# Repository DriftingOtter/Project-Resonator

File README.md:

# Project Resonator | *The* Open-Source IEM Initiative
> A love letter to the IEM/CIEM hobby.

**📖 Documentation Website:** [https://driftingotter.github.io/Project-Resonator-Web/](https://driftingotter.github.io/Project-Resonator-Web/)

---

## What is Project Resonator?

Project Resonator is a comprehensive knowledge base and resource repository for the complete design cycle and engineering development of in-ear monitors (IEMs). The project aims to bridge the gap between hobbyist curiosity and professional-grade IEM development by providing both the technical resources and educational foundation needed to understand and create high-fidelity audio devices.

### Core Resources

Project Resonator provides a complete suite of engineering resources:

- **CAD Shell Design Files** — Parametric 3D models for ergonomic IEM housings
- **Crossover Simulation Circuits** — Fully documented acoustic crossover networks in VituixCAD
- **PCB Design Files** — Production-ready circuit board layouts in KiCad format
- **Driver Characterization Data** — Frequency response and impedance measurements for balanced armature, dynamic, and electrostatic drivers

These resources are designed for both DIY enthusiasts exploring personal audio projects and aspiring entrepreneurs researching entry into the IEM market who may lack formal training in acoustics or electrical engineering.

### Educational Framework

Beyond physical assets, Project Resonator's primary value lies in its structured tutorial system that demystifies each stage of IEM development:

- **Driver Technology & Selection** — Understanding the physics and performance characteristics of transducer types
- **Crossover Circuit Design** — Acoustic filter theory and frequency division network topology
- **PCB Engineering in KiCad** — Translating schematic designs into manufacturable circuit boards
- **CAD Modeling for Acoustics** — Shell geometry, acoustic chambers, and sound bore design in Fusion 360

By consolidating these resources into a single, cohesive repository, Project Resonator enables users to understand the technology they use daily and provides a foundation for experimentation, innovation, and research & development in personal audio.

### Open-Source Collaboration

The open-source nature of this project allows the community to contribute to a centralized knowledge base, helping others in the same pursuit by:

- Improving and expanding existing documentation
- Contributing additional design files and measurement data
- Sharing novel tuning approaches and manufacturing techniques
- Building supplementary tools and resources for IEM development

Project Resonator serves as a living resource that evolves with the IEM community, fostering innovation through shared knowledge and collaborative development.

---

## The Reference Design (Template)

While the guides apply to *any* IEM project, we provide a complete set of files for a specific "Reference" model to get you started.

**Configuration:** All-BA 4-Driver (1× Low + 1× Mid + 2× High)

**Drivers:**
- Knowles CI-22955 (Low)
- Knowles BK-26824 (Mid)
- Knowles SWFK-31736 (Highs)

**Target Tuning:** Similar to the *Moondrop x Crinacle DUSK*

**Estimated Build Cost:** ~$200-300

### Reference Crossover Diagram

```mermaid
graph LR
    Input[Source Input] --> Woofer_Path[Woofer Path<br/>CI-22955]
    Input --> Mid_Path[Mid Path<br/>BK-26824]
    Input --> High_Path[High Path<br/>SWFK-31736]
    
    Woofer_Path --> R1[22Ω Series]
    R1 --> C1[4.7µF Parallel]
    C1 --> Woofer[CI-22955<br/>BA Woofer]
    
    Mid_Path --> C2[10µF Series]
    C2 --> R2[22Ω Series]
    R2 --> C3[4.7µF Parallel]
    C3 --> Mids[BK-26824<br/>BA Mids]
    
    High_Path --> T1_Path[Tweeter 1]
    High_Path --> T2_Path[Tweeter 2]
    
    T1_Path --> C4[2.2µF Series]
    C4 --> R3[6.8Ω Parallel]
    R3 --> Tweeter1[SWFK-31736<br/>Unit A]
    
    T2_Path --> C5[2.2µF Series]
    C5 --> R4[22Ω Parallel]
    R4 --> Tweeter2[SWFK-31736<br/>Unit B]
    
    style Woofer fill:#1a1a1a
    style Mids fill:#1a1a1a
    style Tweeter1 fill:#1a1a1a
    style Tweeter2 fill:#1a1a1a
    style Input fill:#1a1a1a
```

**Note:** The reference tuning is highly individualized. The project's purpose is to provide all necessary tools and resources pre-configured, allowing you to use this as a foundation to tune and create an IEM tailored to your preferences.

---

## 🔧 Technologies Used & Software Required

1. **VituixCAD** — Tuning simulation and acoustic crossover design
2. **KiCad** — Schematic and PCB design
3. **Autodesk Fusion 360** — CAD modeling for IEM shells
4. **FPGraphTracer** — Extracting frequency and impedance responses from driver spec sheets

**Additional Resources:**
- [YouTube Playlist: IEM Building Resources](https://youtube.com/playlist?list=PL4ahDGGN5zBFhmGqVUoBdOnjuF_9HXV5L)
- [Full Documentation Website](https://driftingotter.github.io/Project-Resonator-Web/)

---

## 🛠️ Installation & Setup Guide

### VituixCAD Setup

1. Download VituixCAD from [https://kimmosaunisto.net/](https://kimmosaunisto.net/)
2. Install and open the `.vxp` simulation file included in this repository
3. **Fix missing file paths:**
   - You'll likely see "missing file path" errors on first load
   - Click the folder icon next to each `.frd` or `.zma` file slot
   - Navigate to the `BA Driver Spec Sheets` folder in this repo
   - Re-link the appropriate files for each driver

*(This only needs to be done once per project file)*

### Downloading IEM Shell Files

All IEM shell files are hosted externally on **MEGA** due to GitHub's file size limitations.

🔗 **[Download Shell Files from MEGA](https://mega.nz/folder/2Z4WzYDR#g-NULd1YQFsHa81YXLZzIw)**

The archive includes:
- **Ready-To-Print** — `.stl` files for direct 3D printing
- **Fusion-Shell-Models** — Editable `.f3d` files for customization in Fusion 360

---

## 📚 Documentation

Complete guides are available on the [Project Resonator Documentation Website](https://driftingotter.github.io/Project-Resonator-Web/), including:

### Engineering & Design
- [Driver Selection](https://driftingotter.github.io/Project-Resonator-Web/docs/Driver-Selection)
- [Crossover Design](https://driftingotter.github.io/Project-Resonator-Web/docs/Crossover-Design)
- [Crossover Tuning](https://driftingotter.github.io/Project-Resonator-Web/docs/Crossover-Tuning)
- [Component Picking](https://driftingotter.github.io/Project-Resonator-Web/docs/Component-Picking)

### Manufacturing & CAD
- [PCB Design](https://driftingotter.github.io/Project-Resonator-Web/docs/PCB-Design)
- [Shell Design](https://driftingotter.github.io/Project-Resonator-Web/docs/Shell-Design)
- [Shell Material and Manufacturing](https://driftingotter.github.io/Project-Resonator-Web/docs/Shell-Material-and-Manufacturing)

### Project Information
- [Tools & Software](https://driftingotter.github.io/Project-Resonator-Web/docs/Tools-&-Software)
- [Project Goals & Philosophy](https://driftingotter.github.io/Project-Resonator-Web/docs/Project-Goals-Philosophy)
- [Project Licensing and Usage](https://driftingotter.github.io/Project-Resonator-Web/docs/Project-Licensing-and-Usage)
- [FAQ & Troubleshooting](https://driftingotter.github.io/Project-Resonator-Web/docs/FAQ-Troubleshooting)
- [How to Contribute](https://driftingotter.github.io/Project-Resonator-Web/docs/Contribution)

---

## ❓ Can I Use These Files To Build My Own IEM?

**Absolutely.** This project is licensed under **CERN-OHL-W** (weakly reciprocal), which allows you to:

- Build IEMs for personal use
- Modify and improve the designs
- Use this as a foundation for commercial projects

The license maintains the open-source spirit while being permissive enough for commercial applications. For full details, see the [Project Licensing and Usage](https://driftingotter.github.io/Project-Resonator-Web/docs/Project-Licensing-and-Usage) documentation.

**Note:** This design represents a learning journey and is far from perfect—but it provides a solid foundation and realistic look at what an IEM build process entails. Use it as a starting point to avoid some of the mistakes made along the way.

---

## 🤝 Contributing

Project Resonator welcomes contributions from the community! Whether you're improving documentation, adding measurement data, sharing tuning variants, or fixing errors, your input helps everyone.

See the [Contribution Guide](https://driftingotter.github.io/Project-Resonator-Web/docs/Contribution) for details on how to get involved.

---

## 🚧 Current Status & Community Testing

**Important:** The reference design has not yet been physically tested by the project author due to budget constraints (~$300 build cost). If you build this design, your feedback and measurements would be invaluable to the community. Please share your results and listening impressions!

---

## 👨‍💻 Author

**Daksh Kaul** (DriftingOtter)

---

## 🙌 Credits & Acknowledgments

Special thanks to:

- **Head-Fi DIY IEM Community** — For fostering knowledge sharing and experimentation
- **[Kozh](https://www.youtube.com/@kozh4013/videos)** — IEM design tutorials and insights
- **[Kirby Meets Audio](https://youtu.be/QClvPIuW3zI)** — Driver selection and acoustic theory
- **[Crinacle](https://www.youtube.com/watch?v=tCqV3ZRcZ9g)** — Measurement methodology and target curves
- **[Mr.T's Design Graveyard](https://youtu.be/3FGNw28xBr0)** — PCB design techniques

*If I've forgotten to credit you, please reach out—contributions are always acknowledged.*

---

## 📄 License

This project is licensed under **CERN Open Hardware Licence Version 2 - Weakly Reciprocal** (CERN-OHL-W).

See [LICENSE](./LICENSE) or the [Project Licensing Documentation](https://driftingotter.github.io/Project-Resonator-Web/docs/Project-Licensing-and-Usage) for full details.

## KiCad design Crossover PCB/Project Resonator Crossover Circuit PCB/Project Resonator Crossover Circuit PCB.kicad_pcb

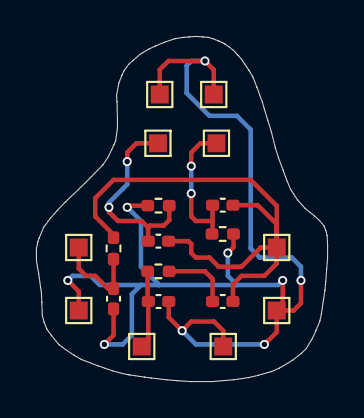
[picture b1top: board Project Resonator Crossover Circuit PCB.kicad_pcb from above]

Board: 2 copper layers, 16.2 x 19.2 mm, 19 parts (0 on the bottom side), 2 nets.

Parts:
C1: 10uF; C_0402_1005Metric_Pad0.74x0.62mm_HandSolder
C2, C6: 2.2uF; C_0402_1005Metric_Pad0.74x0.62mm_HandSolder
C4: 0.10uF; C_0402_1005Metric_Pad0.74x0.62mm_HandSolder
C5: 4.7uF; C_0402_1005Metric_Pad0.74x0.62mm_HandSolder
H1: CI PAD (+); TestPoint_Pad_1.0x1.0mm
H2: CI PAD (-); TestPoint_Pad_1.0x1.0mm
H3: BK PAD (+); TestPoint_Pad_1.0x1.0mm
H4: BK PAD (-); TestPoint_Pad_1.0x1.0mm
H5: SWFK #1 PAD (+); TestPoint_Pad_1.0x1.0mm
H6: SWFK #1 PAD (-); TestPoint_Pad_1.0x1.0mm
H7: SWFK #2 PAD (+); TestPoint_Pad_1.0x1.0mm
H8: SWFK #2 PAD (-); TestPoint_Pad_1.0x1.0mm
H9: SOURCE PAD (+); TestPoint_Pad_1.0x1.0mm
H10: SOURCE PAD (-); TestPoint_Pad_1.0x1.0mm
R2, R5, R6: 22R; R_0402_1005Metric_Pad0.72x0.64mm_HandSolder
R3: 6.8R; R_0402_1005Metric_Pad0.72x0.64mm_HandSolder

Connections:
+: C1.1, C2.1, C2.2, C4.1, C4.2, C5.1, C6.1, C6.2, H1.1, H3.1, H5.1, H7.1, H9.1, R2.1, R2.2, R3.1, R5.1, R5.2, R6.1
GND: C1.2, C5.2, H2.1, H4.1, H6.1, H8.1, H10.1, R3.2, R6.2

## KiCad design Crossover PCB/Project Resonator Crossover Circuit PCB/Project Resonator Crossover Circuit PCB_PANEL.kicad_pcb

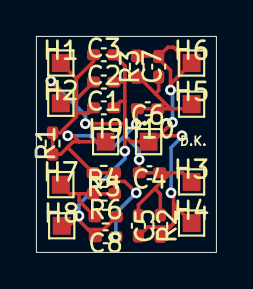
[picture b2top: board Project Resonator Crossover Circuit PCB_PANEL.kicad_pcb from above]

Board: 2 copper layers, 10.0 x 12.0 mm, 24 parts (0 on the bottom side), 2 nets.

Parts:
C1, C2, C3: 100u; C_0402_1005Metric_Pad0.74x0.62mm_HandSolder
C4: 0.027u; C_0402_1005Metric_Pad0.74x0.62mm_HandSolder
C5: 4.7u; C_0402_1005Metric_Pad0.74x0.62mm_HandSolder
C6: 0.008u; C_0402_1005Metric_Pad0.74x0.62mm_HandSolder
C7: 2.2u; C_0402_1005Metric_Pad0.74x0.62mm_HandSolder
C8: 10u; C_0402_1005Metric_Pad0.74x0.62mm_HandSolder
H1, H3, H5, H7, H9: + MountingHole_Pad; TestPoint_Pad_1.0x1.0mm
H2, H4, H6, H8: - MountingHole_Pad; TestPoint_Pad_1.0x1.0mm
H10: MountingHole_Pad; TestPoint_Pad_1.0x1.0mm
R1: 5600R; R_0402_1005Metric_Pad0.72x0.64mm_HandSolder
R2: 22R; R_0402_1005Metric_Pad0.72x0.64mm_HandSolder
R3: 10000R; R_0402_1005Metric_Pad0.72x0.64mm_HandSolder
R4: 6800R; R_0402_1005Metric_Pad0.72x0.64mm_HandSolder
R5: 0.092R; R_0402_1005Metric_Pad0.72x0.64mm_HandSolder
R6: 6.8R; R_0402_1005Metric_Pad0.72x0.64mm_HandSolder

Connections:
+: C1.1, C2.1, C3.1, C4.1, C4.2, C5.1, C6.1, C6.2, C7.1, C8.1, H1.1, H3.1, H5.1, H7.1, H9.1, R1.1, R1.2, R2.1, R3.1, R4.1, R4.2, R5.1, R5.2, R6.1
GND: C1.2, C2.2, C3.2, C5.2, C7.2, C8.2, R2.2, R3.2, R6.2

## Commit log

2025-03-23 my passion project
2025-03-23 removed software files, and old files not used for project
2025-03-23 Accdentally removed BA driver measurements
2025-03-23 compressed SHELL Files with OpenCTM
2025-03-23 Added Dropbox link for IEM Shell files
2025-03-23 fixed spelling mistake in README
2025-03-23 clarified decompression process in readme
2025-03-24 Added Github README Banner
2025-03-24 Updated Banner Path
2025-03-24 fixed decompress heading spelling mistake and moved credits from authors to seperate section
2025-03-24 Update README.md and cleared up install guide for VituixCAD
2025-03-24 Update README.md to corrrect URL for VituixCAD
2025-03-24 fixed 'archived' spelling mistake
2025-03-24 Update README.md to show clariety in navigating the project folder during vituixCAD install guide
2025-03-27 modified crossover to use 2nd order low pass instead of high capacitance series chains
2025-04-04 MAJOR UPDATE: Improved Crossover to reduce redudent componets from 15 -> 10, Improved subbass isolation, updated PCB to reflect changes, added v3 shell images to assets, uploaded new gerber and drill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
2025-04-04 Updated README to include Morten Arnoldus's measurements for Knowles BA drivers && included files to the BA drivers measurements directory
2025-04-04 Added the compressed Gerber and Drill Files of the new PCB overall
2025-04-04 updated PCB to connect ground pour to GND and make track size to 8mils and fixed clearence issues
2025-04-04 updated crossover to have ~5-6db cut at 10k to match shell material high frequency resonace (updated CROSSOVER, SCHEMATIC, PCB, GERBER, and DRILL FILES
2025-04-04 forgot to add the compressed .zip for the high frequnecy cut
2025-04-08 updated 800ohm to 750ohm for product resistor in use from JLCPCB, updated ground and added 1 more resistor for CI driver, updated gerber and drill files and updated crossover ciruit to match changes
2025-04-24 Added development timeline to README
2025-04-24 fixed commign soon tag to be lower
2025-04-24 moved IEM shell files from dropbox to mega for more space && added orginal fusion files for people to use and modifty
2025-04-24 Updated README to include new MEGA link and also make the writting more concise
2025-04-24 removed excessive break linkes from README
2025-04-24 Added Mermaid Diagram Of Crossover Circuit
2025-04-24 Moved Diagram to README and fixed some mispellings and created common positive and ground
2025-04-24 updated timeline in README
2025-05-29 feat: Added Bluetooth Support Via feasycom's FSC-BT6038A module && configuration utility tool && updated readme to reflect changes
2025-08-25 Redesigned Layout of PCB to Wrap Shell, Updated Overall Shell Design, Removed Bluetooth Code experimental, Rendered New colorways mockups
2025-08-25 Removed README section regarding bluetooth experimental module
2025-09-15 moved to latest version of vituixCAD and ported crossover files, and moved old version to legacy directory, and also removed SMD componenet list directory due to deprecation
2025-09-15 updated readme to match the changes
2025-09-15 removed old bluetooth technology requirements
2025-09-19 updated crossover to fit purchased components assortment (minor tweaks, almost exactly the same), and added SWFK 3D model
2025-09-19 Updated crossover diagram to set labels to drivers correctly from sub-to-air, and updated crossover capacitance and resistance values
2025-09-21 Added youtube playlist for iem building as addional resource till all wiki guides are made
2025-10-22 updated crossover circuit and moved old crossover to legacy folder
2025-11-11 Fix checkmarks and update crossover diagram
    Corrected checkmarks in development timeline and updated crossover diagram for clarity.
2025-12-29 added wiki entry image assets to repo
2025-12-29 added wiki image assets for shell guide
2025-12-29 Delete wiki_assets/Screenshot 2025-12-28 at 10.53.08 PM.png (driver cutout extortion image)
    wasn't showing the actual red extrusion zone
2025-12-30 updated readme to show the website
2026-01-01 updated PCB crossover to match the latest crossover diagram and fixed size to fit latest version of the shell
2026-01-01 downloaded updated drill files
